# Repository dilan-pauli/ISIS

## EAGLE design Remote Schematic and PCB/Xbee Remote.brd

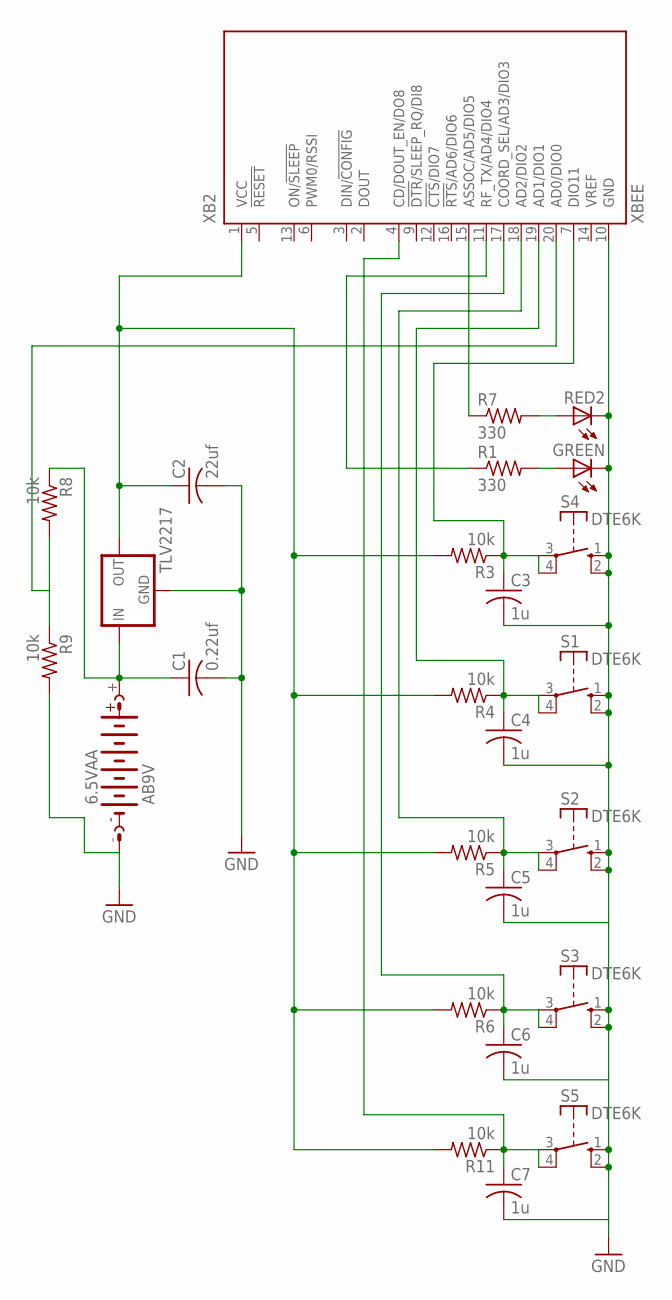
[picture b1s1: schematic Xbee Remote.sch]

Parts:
6.5VAA: AB9V
C1: 0.22uf; C025-024X044
C2: 22uf; C025-024X044
C3, C4, C5, C6, C7: 1u; C025-024X044
GREEN: LED5MM
R1, R7: 330; 0204/5
R3, R4, R5, R6, R8, R9, R11: 10k; 0204/5
RED2: LED5MM
S1, S2, S3, S4, S5: DTE6K
TLV2217: 78XXS
XB2: XBEE

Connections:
GND: 6.5VAA.-, C3.2, C4.2, C5.2, C6.2, C7.2, GREEN.K (C), R9.2, RED2.K (C), S1.1 (S), S1.2 (S), S2.1 (S), S2.2 (S), S3.1 (S), S3.2 (S), S4.1 (S), S4.2 (S), S5.1 (S), S5.2 (S), XB2.10 (GND)
unnamed: GREEN.A, R1.2
unnamed: 6.5VAA.+, C1.1, R8.1, TLV2217.IN
unnamed: C2.1, R3.2, R4.2, R5.2, R6.2, R11.2, TLV2217.OUT, XB2.1 (VCC)
unnamed: C7.1, R11.1, S5.3, S5.4, XB2.4 (CD/DOUT_EN/DO8)
unnamed: C1.2, C2.2, TLV2217.GND
unnamed: R1.1, XB2.11 (RF_TX/AD4/DIO4)
unnamed: R7.2, RED2.A
unnamed: R8.2, R9.1, XB2.20 (AD0/DIO0)
unnamed: C5.1, R5.1, S2.3, S2.4, XB2.18 (AD2/DIO2)
unnamed: C3.1, R3.1, S4.3, S4.4, XB2.7 (DIO11)
unnamed: C6.1, R6.1, S3.3, S3.4, XB2.17 (COORD_SEL/AD3/DIO3)
unnamed: R7.1, XB2.15 (ASSOC/AD5/DIO5)
unnamed: C4.1, R4.1, S1.3, S1.4, XB2.19 (AD1/DIO1)

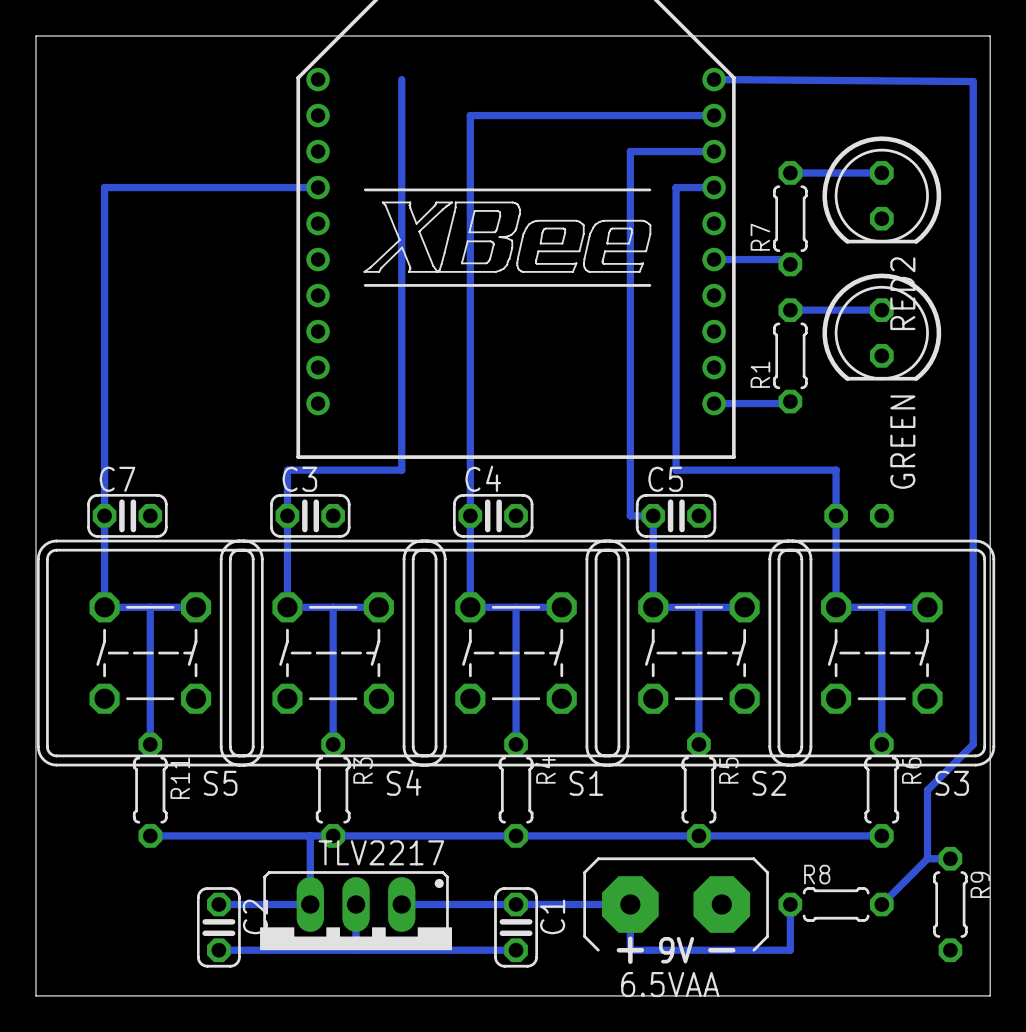
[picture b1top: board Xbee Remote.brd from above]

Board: 2 copper layers, 53.0 x 53.3 mm, 26 parts (1 on the bottom side), 14 nets.

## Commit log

2013-01-13 Initial Server Process Commit
    Code for the WebSocketApplication and Websocket connections. Start
    point.
    Glassfish server is used.
    Initial WebContent to be used to test the WebSocket server.
2013-01-14 Adding the XBEE interface project
2013-01-15 WebSocket improvements
    Test client HTML page has been improved on to connect to the WebSocket
    server. Client can make requests and the server can push data to the
    client. At this point, all the server does is push useless messages to
    the server. Since communication can now occur in both directions using
    the same WebSocket connection, the next step is to link the two to send
    useful messages (echo back whatever a client sends). Current code does
2013-01-17 Adding the xbee class again i messed it up.
2013-01-17 Adding Java libs for the xbee
2013-01-17 Deleted the XBEE interface class and created the ISIS server eclipse project. This can be pulled down and edited by anyone. the libs for the xbee are included. Dwight will need to add the websocket l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
2013-01-18 Basic WebSocket echo functionality now working
    Can now get the server to send a client's message back through
    WebSocket connection. Next step would be to modify the server to parse
    and act on data as specified by a communication interface that will
    have to be designed. (Consider JSON for defining the data)
    Future consideration: will need to create embedded Glassfish server so
    that it can be started up within the ISIS main application (while
2013-01-18 Revert "Basic WebSocket echo functionality now working"
    This reverts commit 74fa4db5eae97e9a6d1c828f9805e6e114806a2b.
2013-01-18 Revert "Revert "Basic WebSocket echo functionality now working""
    This reverts commit 5ead168359fee041792e70a2c97ad7331b519b35.
2013-01-18 Revert "Revert "Basic WebSocket echo functionality now working""
    This reverts commit 97f3c72d4f80a3332ba815cd6e53f53b16b3de12.
2013-01-18 Revert "Revert "Revert "Basic WebSocket echo functionality now working"""
    This reverts commit 1d0d2bc0f6e7b071ada93afc6fa9726dfed7e55a.
2013-01-21 Adding test class back
2013-02-02 Added all of the stub files for most of the ISIS funtions. ALso added some of the missing libarys to the build path and started to flesh out the XBee handeler class.
2013-02-03 deleted the glass fish lib roo big
2013-02-04 Updated the XBee side
2013-02-05 Start-point for WebSocket Object component of the design
    Implemented several classes and interfaces that would be required.
    Added a JSON library to use.
2013-02-06 changed some stuff in the test class
2013-02-07 Updated the xbee test class to include the led feed back. May need some tweaking to get it to stay n with multiple button presses but it is a good start and will be useful in the XBee handler class.
2013-02-09 Changed the way that we envisioned the remote. I created a Remote interface and kept the queues inside of the the XBee handler class. THis will allow for better modularity hopfully. Will need to conf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
2013-02-09 Added new WebSocket stuff. Issues deploying web application on embedded GlassFish 3.1.2 though.
2013-02-09 Added WebSocket server test.
2013-02-12 Added some more code in WebSockerServer to try deploying the web application as a war file. Did not work. Still get the same errors as with the ScatteredArchive approach. Moved some web content files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
2013-02-14 Removed com.sun.grizzly.util.jar from the build path. Seems there was some code in theres that was causing deploy problems with embedded GlassFish. With this removed, application can now be deployed 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
2013-02-20 Started work on Controller. Added method stubs and description of things that need to be done within the control package.
    Also adding some slight webSock changes occurring during the testing of
    embedded GlassFish. Still have error where everything starts up well and
    the application gets deployed but the index.jsp resource is not found
    when testing this in a browser.
2013-02-20 Added some methods and data structures to Controller. Wrote methods for Xbee state.
2013-02-20 Some more Controller and XbeeState coding
2013-02-21 Some more work on the Controller and its Threads
2013-02-21 Adjustments to Main, the Controller and its threads. Threads just do a dummy task at the moment. Next step would be to run the entire thing and check whether the threads run as expected before fillin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
2013-02-22 Code architecture restructuring. Main difference is that Main.java no longer runs the whole show ISISServerApplication does now (did not delete old classes yet anyway - will do so later). There is no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
2013-02-22 Code restructuring in progress. Converted project directory to Dynamic Web Application format required. Currently has problems deploying ISISServer on GlassFish due to class not found exception for X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
2013-02-25 Removing top level unused src
2013-02-25 Adding the finished XBee handler and the interfaces to go with it.
2013-02-25 Adding updated xbee test.
2013-02-25 remove this duplicate lib
2013-02-25 remove unneeded folders
2013-02-26 Added some test info to the xbeehandler. Also edited Thread1 to have bare bones. need to talk to dwight about the websocket part and need to plan out the remoteDeviceState List.
2013-02-26 Updated WebSock side
2013-02-26 FInalized the inputs for the threads 1 and 2 they sould not need to be shanged now. Dwight should we be deleting main?
2013-02-26 Took dwights Xbee State class and replaced my XBee packet class with it. Also tunred the xbee hashmap into a remote data map for modularity. The controller really doesnt need to know about XBEEs it s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
2013-02-26 Updated the XBee handler to set the packet correctly
2013-02-27 Changed the way the controller class handles the logical and physical addresses. All that need to be done for this class is the JSON stuff and deal with timer thread (which may or may not be existing)
2013-02-27 THread 1 should now be fit for testing, and thread 2 is set up just to init the state list by sending out on init command. The packet filling funtion in handler is also complete now.
2013-02-27 MAJOR RESTRUCTURE POINT. STUFF WORKS FINE IN THIS ONE ALL THINGS CONSIDERED
2013-02-27 Added project settings to repo
2013-03-01 Wrote regression tests for WebSocket Queues and Interfaces, WebSocket Receiver, WebSocket Sender
2013-03-02 Wrote JSONObject to XBeePacket (and vice-versa) functions within Controller. Fixed small issue with physicalToLogical(...)
2013-03-02 Put everything together. Only Thread2 is excluded from the initial code to be used for system test run
2013-03-04 Updated all files for the project so far. Dry system test run allowed transmission of button events from test controllers to the browser. Thread 2, which handles incoming requests from browser client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
2013-03-05 Added code for Thread2. Still not included in Controller though so it would not start
2013-03-05 Added Dilan's Xbee updates
2013-03-05 Commented in code for running Thread2 also and catching exception within it in case of invalid requests
2013-03-05 Updated some errors in attempt to fix Thread2 exceptions
2013-03-09 Updated version of ISIS. Thread 2 has been debugged: Previous conversion errors and exceptions have been taken care of
2013-03-09 Slight modifications to jsp to display sent message details. Non-API messages still not well handled beyond catching exceptions. Want error message sent back
2013-03-09 Added a way for the timer thread to check the state list and assign a off position to the xbees that have not checked in in the last 30 sec of operation. Also when a remote state is placed in the sta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
2013-03-09 Added in initialization request handling capability. Everything else still works
2013-03-11 Adding the Schematic and the PCB design for the first type of hardware.
2013-03-11 Adding the src code for the anderzon webgame
2013-03-14 Web game improvement. Added the interface to ISIS controller. Game can now be controlled by the keyboard and the ISIS controller even at the same time. Collisions betweent the player and the wall, pl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
2013-03-15 Added some XBee disconnection handling to ensure the entire application gets killed
2013-03-16 Adding the changes to kill the threads
2013-03-28 Updated helicopter game. Game logic does not have full win and lose handling yet. All collisions work. Game menu included. Currently has a bug with being hit by the boss's fireball.
2013-03-28 Fixed previously mentioned bugs in the helicopter game. Now need to handle defeat and win properly with good game clean up routines. Right now the game interval simply gets killed and everything free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
2013-03-28 Improved game ending scenario handling. Need to add listeners to return to main menu
2013-03-28 Updated version of the helicopter game. Bugs have been worked out. Game victory and defeat are now handled well
2013-03-29 Added mute functionality. Added difficulty functionality. Finished options menu
2013-03-29 Web Game has been completed. Final screen bugs worked out.
2013-03-29 Web Game has been completed. Corrected old index.php file to be same as new index.html. Previously forgot to update the php
2013-04-27 Updated the WebGame. Old version did not have the complete version with game kill and end scenarios
